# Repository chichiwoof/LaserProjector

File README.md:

Teensy Laser implementation on code from Deltaflo
http://www.instructables.com/id/Arduino-Laser-Show-With-Real-Galvos/

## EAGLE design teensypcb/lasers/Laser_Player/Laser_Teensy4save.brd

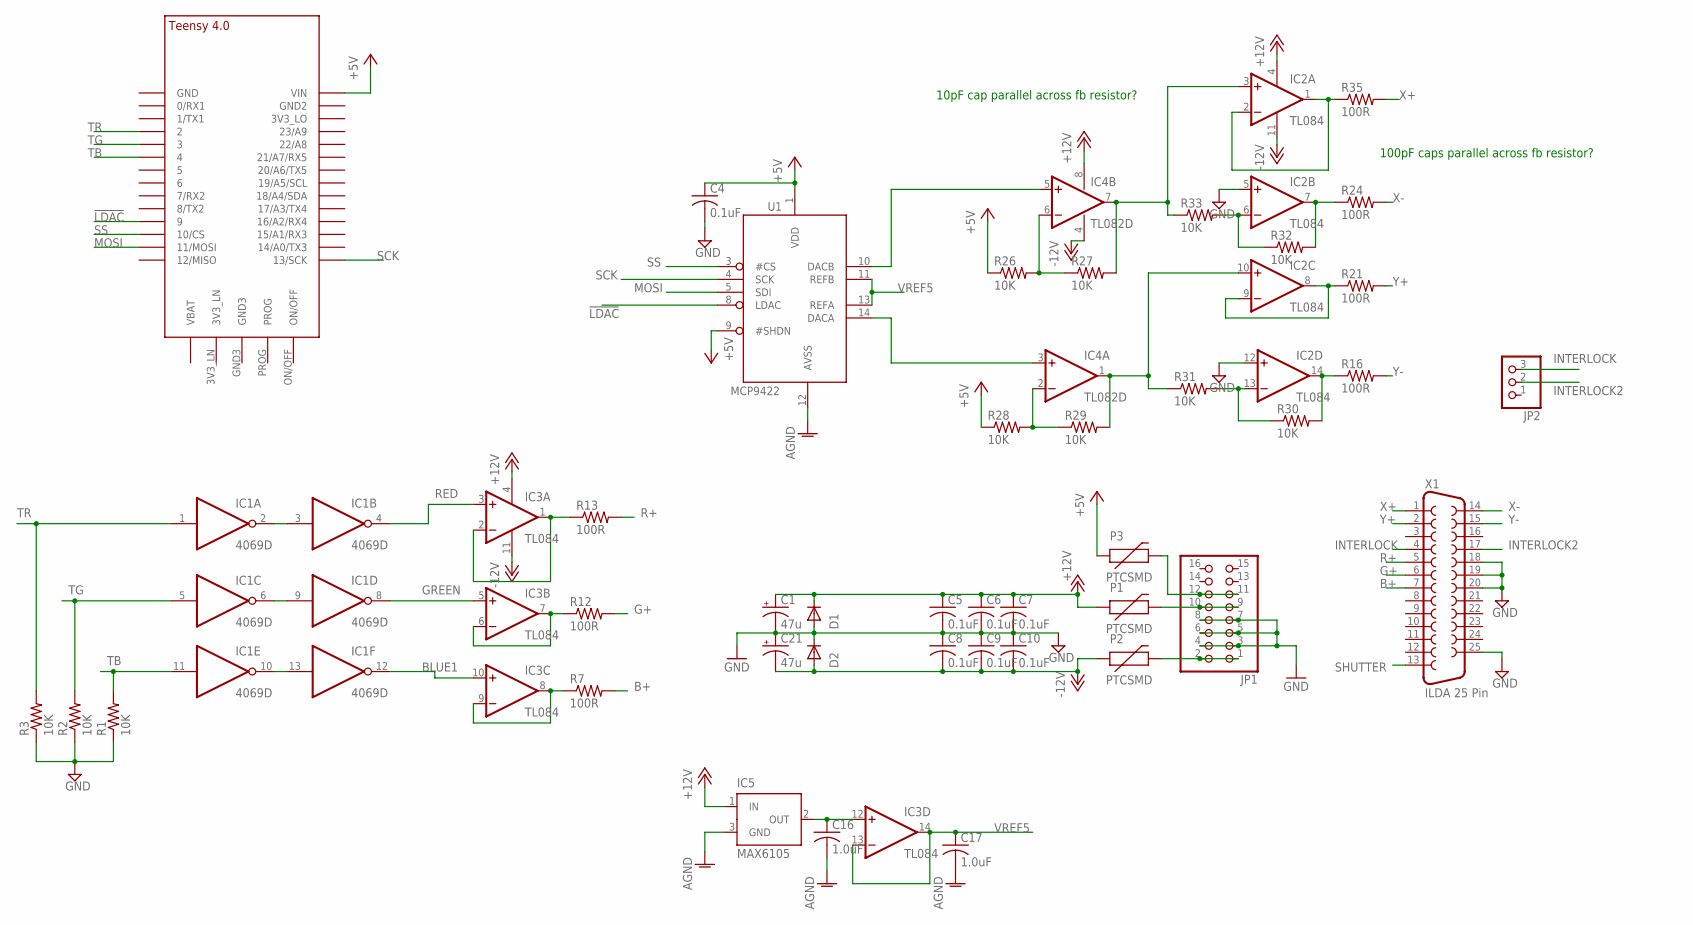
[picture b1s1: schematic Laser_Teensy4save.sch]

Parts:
C1, C21: 47u; PANASONIC_D
C4, C5, C6, C7, C8, C9, C10: 0.1uF; C0603
C16, C17: 1.0uF; C025-024X044
D1, D2: 1N5819HW; SOD123
IC1: 4069D; SO14
IC2, IC3: TL084; SOIC-14
IC4: TL082D; SO08
IC5: MAX6105; SOT23
JP1: PINHD-2X8; 2X08
JP2: PINHD-1X3; 1X03
P1, P2, P3: PTCSMD; PTC-1206
R1, R2, R3, R26, R27, R28, R29, R30, R31, R32, R33: 10K; R0603
R7, R12, R13, R16, R21, R24, R35: 100R; R0603
U1: MCP4922; SOIC-14
U$1: TEENSY_4.0
X1: ILDA 25 Pin; F25D

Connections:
!LDAC: U1.8 (LDAC), U$1.9/CS (9)
+5V: C4.1, IC1.14 (VDD), P3.1, R26.1, R28.1, U1.1 (VDD), U1.9 (#SHDN), U$1.VIN
+12V: C1.+, C5.1, C6.1, C7.1, D1.C, IC2.4 (V+), IC3.4 (V+), IC4.8 (V+), IC5.1 (IN), P1.1
-12V: C8.2, C9.2, C10.2, C21.-, D2.A, IC2.11 (V-), IC3.11 (V-), IC4.4 (V-), P2.1
AGND: C16.2, C17.2, IC5.3 (GND), U1.12 (AVSS)
B1+: IC3.8 (OUT), IC3.9 (-IN), R7.1
B+: R7.2, X1.7
BLUE1: IC1.12 (O), IC3.10 (+IN)
G1+: IC3.1 (OUT), IC3.2 (-IN), R13.1
G+: R12.2, X1.6
GND: C1.-, C4.2, C5.2, C6.2, C7.2, C8.1, C9.1, C10.1, C21.+, D1.A, D2.C, IC2.5 (+IN), IC2.12 (+IN), JP1.3, JP1.4, JP1.5, JP1.6, JP1.7, JP1.8, R1.1, R2.1, R3.1, X1.18, X1.19, X1.20, X1.25
GREEN: IC1.8 (O), IC3.5 (+IN)
INTERLOCK: JP2.3, X1.4
INTERLOCK2: JP2.2, X1.17
MOSI: U1.5 (SDI), U$1.11/MOSI
unnamed: IC1.2 (O), IC1.3 (I)
unnamed: IC1.6 (O), IC1.9 (I)
unnamed: IC1.10 (O), IC1.13 (I)
unnamed: JP1.1, JP1.2, P2.2
unnamed: JP1.9, JP1.10, P1.2
unnamed: JP1.11, JP1.12, P3.2
unnamed: IC4.5 (+IN), U1.10 (DACB)
unnamed: C16.1, IC3.12 (+IN), IC5.2 (OUT)
unnamed: IC4.6 (-IN), R26.2, R27.1
unnamed: IC4.2 (-IN), R28.2, R29.1
unnamed: IC4.3 (+IN), U1.14 (DACA)
unnamed: IC2.6 (-IN), R32.1, R33.2
unnamed: IC2.13 (-IN), R30.1, R31.2
R1+: IC3.6 (-IN), IC3.7 (OUT), R12.1
R+: R13.2, X1.5
RED: IC1.4 (O), IC3.3 (+IN)
SCK: U1.4 (SCK), U$1.13/SCK
SHUTTER: X1.13
SS: U1.3 (#CS), U$1.10/CS
TB: IC1.11 (I), R1.2, U$1.4/CANRX (4)
TG: IC1.5 (I), R2.2, U$1.3/CANTX (3)
TR: IC1.1 (I), R3.2, U$1.2
VREF5: C17.1, IC3.13 (-IN), IC3.14 (OUT), U1.11 (REFB), U1.13 (REFA)
VSS: IC1.7 (VSS)
X1+: IC2.1 (OUT), IC2.2 (-IN), R35.1
X1-: IC2.7 (OUT), R24.1, R32.2
X2: IC2.10 (+IN), IC4.1 (OUT), R29.2, R31.1
X+: R35.2, X1.1
X-: R24.2, X1.14
Y1+: IC2.8 (OUT), IC2.9 (-IN), R21.1
Y1-: IC2.14 (OUT), R16.1, R30.2
Y2: IC2.3 (+IN), IC4.7 (OUT), R27.2, R33.1
Y+: R21.2, X1.2
Y-: R16.2, X1.15

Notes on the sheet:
10pF cap parallel across fb resistor?
100pF caps parallel across fb resistor?

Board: 2 copper layers, 44 parts (0 on the bottom side), 47 nets, no tracks yet.

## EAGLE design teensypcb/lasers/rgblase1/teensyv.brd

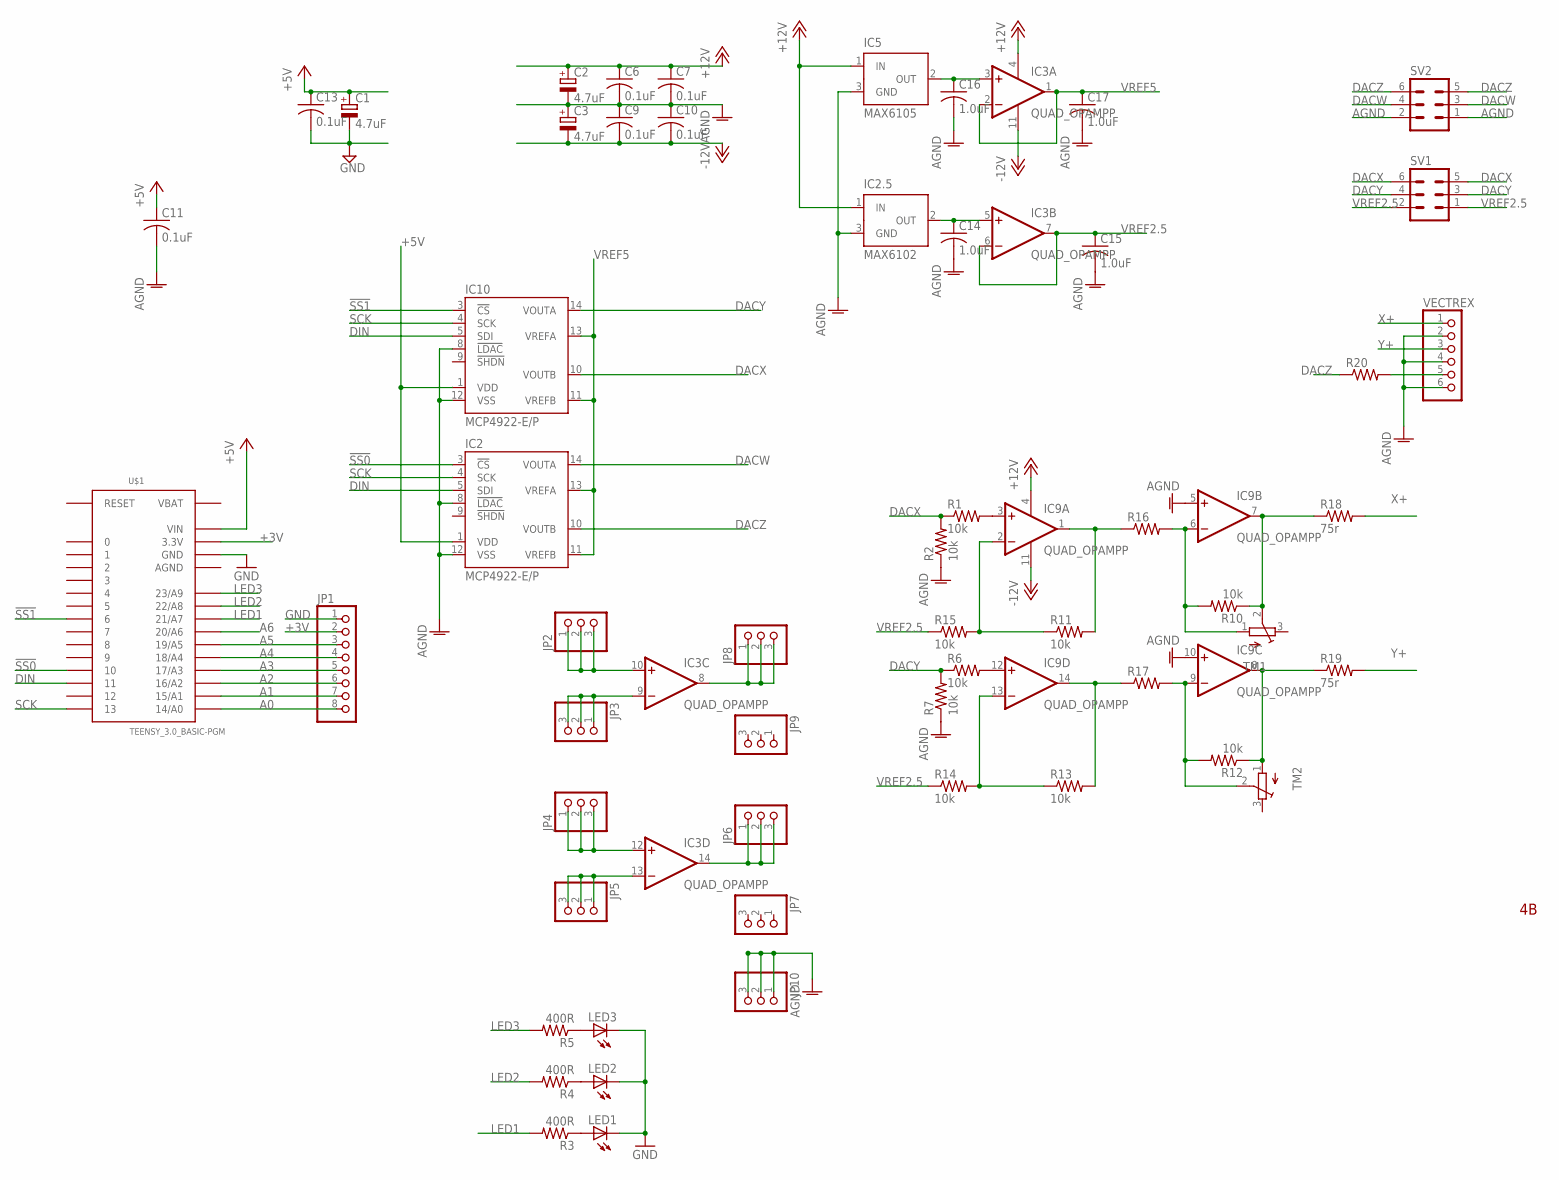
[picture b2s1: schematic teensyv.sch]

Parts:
C1, C2, C3: 4.7uF; E1,8-4
C6, C7, C9, C10, C11, C13: 0.1uF; C025-024X044
C14, C15, C16, C17: 1.0uF; C025-024X044
IC2, IC10: MCP4922-E/P; DIL14
IC2.5: MAX6102; SOT23
IC3, IC9: QUAD_OPAMPP; DIL14
IC5: MAX6105; SOT23
JP1: PINHD-1X8CLEANBIG; 1X08-CLEANBIG
JP2, JP3, JP4, JP5, JP6, JP7, JP8, JP9, JP10: PINHD-1X3; 1X03
LED1, LED2, LED3: LED5MM
R1, R2, R6, R7, R10, R11, R12, R13, R14, R15: 10k; 0204V
R3, R4, R5: 400R; 0204V
R16, R17, R20: R-US_0204/7; 0204/7
R18, R19: 75r; 0204V
SV1, SV2: MA03-2
TM1, TM2: TRIMPOTTC33X; TC33X
U$1: TEENSY_3.0_BASIC-PGM
VECTREX: PINHD-1X6; 1X06

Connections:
!SS0: IC2.3 (!CS), U$1.10
!SS1: IC10.3 (!CS), U$1.6
+3V: JP1.2, U$1.3.3V, U$1.3.3V1 (3.3V)
+5V: C1.+, C11.1, C13.1, IC2.1 (VDD), IC10.1 (VDD), U$1.VIN
+12V: C2.+, C6.1, C7.1, IC2.5.1 (IN), IC3.4 (V+), IC5.1 (IN), IC9.4 (V+)
-12V: C3.-, C9.2, C10.2, IC3.11 (V-), IC9.11 (V-)
A0: JP1.8, U$1.14/A0
A1: JP1.7, U$1.15/A1
A2: JP1.6, U$1.16/A2
A3: JP1.5, U$1.17/A3
A4: JP1.4, U$1.18/A4
A5: JP1.3, U$1.19/A5
A6: U$1.20/A6
AGND: C2.-, C3.+, C6.2, C7.2, C9.1, C10.1, C11.2, C14.2, C15.2, C16.2, C17.2, IC2.8 (!LDAC), IC2.12 (VSS), IC2.5.3 (GND), IC5.3 (GND), IC9.5 (+IN), IC9.10 (+IN), IC10.8 (!LDAC), IC10.12 (VSS), JP10.1, JP10.2, JP10.3, R2.1, R7.1, SV2.1, SV2.2, U$1.AGND, VECTREX.2, VECTREX.4, VECTREX.6
DACW: IC2.14 (VOUTA), SV2.3, SV2.4
DACX: IC10.10 (VOUTB), R1.1, R2.2, SV1.5, SV1.6
DACY: IC10.14 (VOUTA), R6.1, R7.2, SV1.3, SV1.4
DACZ: IC2.10 (VOUTB), R20.1, SV2.5, SV2.6
DIN: IC2.5 (SDI), IC10.5 (SDI), U$1.11
GND: C1.-, C13.2, JP1.1, LED1.K (C), LED2.K (C), LED3.K (C), U$1.GND, U$1.GND1 (GND)
LED1: R3.2, U$1.21/A7
LED2: R4.2, U$1.22/A8
LED3: R5.2, U$1.23/A9
unnamed: C14.1, IC2.5.2 (OUT), IC3.5 (+IN)
unnamed: IC9.3 (+IN), R1.2
unnamed: C16.1, IC3.3 (+IN), IC5.2 (OUT)
unnamed: IC3.13 (-IN), JP5.1, JP5.2, JP5.3
unnamed: IC3.12 (+IN), JP4.1, JP4.2, JP4.3
unnamed: IC3.14 (OUT), JP6.1, JP6.2, JP6.3
unnamed: LED1.A, R3.1
unnamed: IC9.1 (OUT), R11.2, R16.1
unnamed: IC9.12 (+IN), R6.2
unnamed: IC9.2 (-IN), R11.1, R15.2
unnamed: LED2.A, R4.1
unnamed: LED3.A, R5.1
unnamed: IC9.7 (OUT), R10.1, R18.1, TM1.2 (S)
unnamed: IC9.8 (OUT), R12.1, R19.1, TM2.1 (A)
unnamed: IC9.14 (OUT), R13.2, R17.1
unnamed: IC9.9 (-IN), R12.2, R17.2, TM2.2 (S)
unnamed: IC9.6 (-IN), R10.2, R16.2, TM1.1 (A)
unnamed: IC3.9 (-IN), JP3.1, JP3.2, JP3.3
unnamed: IC3.10 (+IN), JP2.1, JP2.2, JP2.3
unnamed: IC3.8 (OUT), JP8.1, JP8.2, JP8.3
unnamed: R20.2, VECTREX.5
SCK: IC2.4 (SCK), IC10.4 (SCK), U$1.13
VBAT: U$1.VBAT
VREF2.5: C15.1, IC3.6 (-IN), IC3.7 (OUT), R14.1, R15.1, SV1.1, SV1.2
VREF5: C17.1, IC2.11 (VREFB), IC2.13 (VREFA), IC3.1 (OUT), IC3.2 (-IN), IC10.11 (VREFB), IC10.13 (VREFA)
X+: R18.2, VECTREX.1
Y+: R19.2, VECTREX.3
YFB: IC9.13 (-IN), R13.1, R14.2

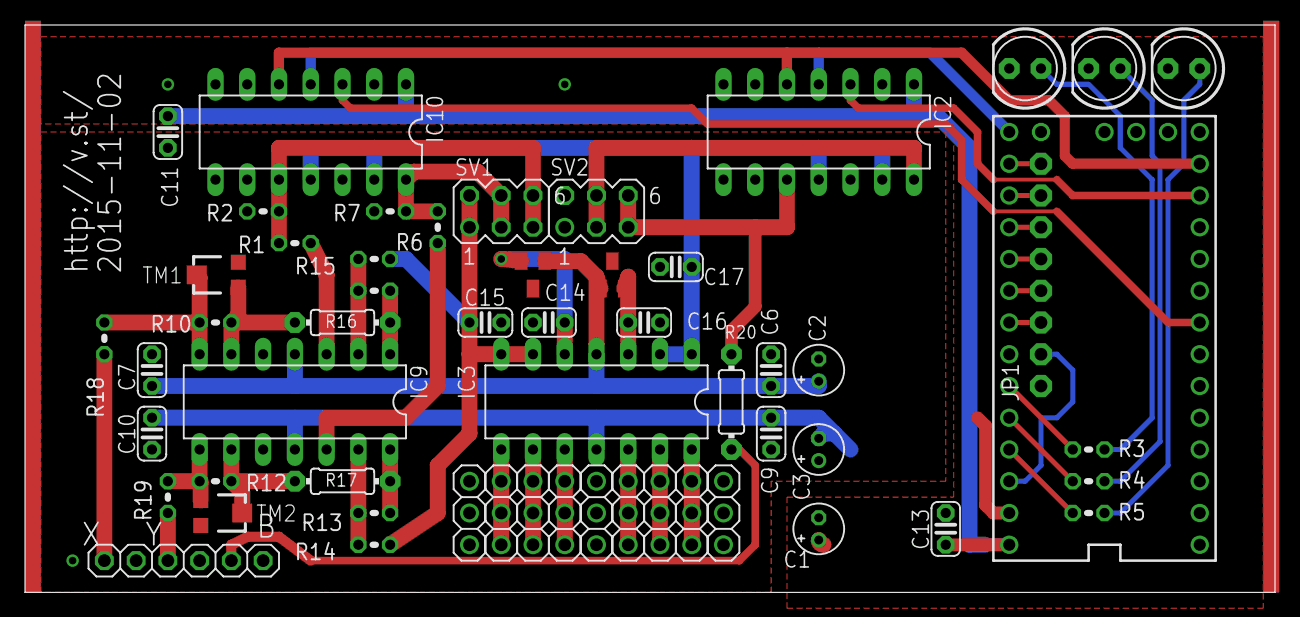
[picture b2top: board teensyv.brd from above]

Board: 2 copper layers, 100.0 x 45.4 mm, 56 parts (0 on the bottom side), 49 nets.

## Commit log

2020-05-27 changed up for mcp4728
2020-05-28 LASERX added and script tests
2020-05-28 try ilda-decoder c and h files no go
2020-05-29 attempts at ilda decoded into gcode nonfunctional
2020-06-11 abopoli
2021-03-11 added pcb stuff
2021-03-31 laser schematic eltn)
